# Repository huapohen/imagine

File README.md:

# 灵伴 LINGBAN / Imagine

透明晶鼠中的原创微型城堡，与电脑上的主动办公伙伴。当前交付是**可运行软件、固件与数字工程原型、商业与路演资料、AI概念影片**；实物样机、认证与量产尚待验证。

## 打开交付

- [本地资料中心](http://127.0.0.1:8766/)：产品图、全部文档、概念影片与评审资料。
- [16页商业计划PDF](pitch/business-plan/lingban-business-plan.pdf) · [商业计划源文](docs/business/business-plan.md)
- [18页可编辑PPTX](pitch/deliverables/final-20260906/lingban-vc-deck.pptx) · [PDF](pitch/deliverables/final-20260906/lingban-vc-deck.pdf) · [离线HTML](pitch/deliverables/final-20260906/lingban-vc-deck.html)
- [3分钟与8分钟逐字稿](docs/business/pitch-scripts.md) · [60个投资人问题](docs/business/investor-qa-60.md)
- [软件启动说明](software/README.md) · [模型接入与真实测试](docs/software/MODEL_INTEGRATION.md) · [固件](firmware/README.md)
- [CAD/PCB工程交接](hardware/COMPLETION.md) · [工厂RFQ](docs/manufacturing-commercial/rfq-template.md) · [独立硬件评审](docs/verification/HARDWARE_REVIEW.md)
- [八条影片与制作验证](media/FINAL_REPORT.md) · [私有GitHub仓库](https://github.com/huapohen/imagine)

## 本地运行

Python 3.9+，软件服务仅使用标准库：

```sh
./software/start.sh
```

按终端显示的员工/企业链接进入。角色令牌是访问凭据，只保存在页面内存；不要把带令牌的链接放进报告。所有默认演示数据均为合成数据，审批结果只进入本地outbox。

本次交付已在8765启动默认离线服务。当前角色链接记录在权限0600、Git忽略且资料服务不提供访问的`.local/demo-server.log`；可在本机终端查看。用户既有Chrome配置曾拦截该端口，未关闭浏览器保护；隔离浏览器验收已通过，录屏可直接查看。

另开终端运行资料中心：

```sh
python3 scripts/serve_workspace.py
```

临时模型测试使用根目录已被Git忽略的`.env`，须按[模型说明](docs/software/MODEL_INTEGRATION.md)显式开启。默认模型为`gpt-6-astra`、推理强度`medium`；模型负责合成场景草稿，本地权限、本人确认和调用预算保持有效。临时配置不进入镜像、交付压缩包或生产环境。

## 验证与交付边界

[最终验收矩阵](docs/verification/RELEASE_READINESS.md)记录自动化、浏览器、协议、固件编译、CAD、KiCad与视频的实际证据及未验证项。

299元是1000台情景下核心版的目标售价；108元制造成本和66.51元单位贡献是模型估算。五台EVT样机的开发板、透明件和装配成本单独计算。融资500万元是建议方案，60万元精简经营模型单独列示，没有收入或融资实绩假设。

企业只获得本人明确分享的业务结果与至少五人的聚合。人数阈值不代表匿名化；不做秘密采集、键盘记录、情绪/生理员工评分或自动雇佣决策。

EVT-A采用OEM USB HID鼠标总成与独立ESP32-S3交互模块、两路USB连接，电脑承担AI。设备唯一线协议是LB1 ASCII + CRC16；MCP 2025-06-18与A2A 0.3.0是本地实现子集。固件可编译、数字检查通过都不能替代实际通电、ESD/EMC、人体工学和工厂DFM签字；制造文件保持**NOT-FOR-FAB**。

大体积影片和制造ZIP通过私有GitHub Release附件分发，源码、财务、文档和精确哈希清单保留在Git。仅克隆仓库时，按[附件清单](docs/operations/RELEASE_ASSETS.md)恢复媒体。没有联系厂家/投资人、租GPU或额外购买工具。

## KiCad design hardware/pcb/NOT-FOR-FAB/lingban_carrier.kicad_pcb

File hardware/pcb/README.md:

# ESP32-S3 交互载板 EVT-A

`NOT-FOR-FAB/lingban_carrier.kicad_pro` 为可编辑工程；同目录包含原理图、实际双面走线PCB、自包含符号/封装库。36×76×1.6mm，2层1oz假设，0.25mm线宽，0.65/0.30mm过孔。所有输出仅工程评审用。

本载板只含插座、限流/上拉阻容、屏/LED/触摸/物理开关线束接口；ESP32-S3、RGB灯、屏幕与DPDT是外部器件。原理图所有引脚是无源载板触点，ERC只证明本载板连接规则；不证明ESP电气配置或外接器件正确。D1为DNI ESD占位，量产必须冻结真实TVS并更改封装/复验。

复现：仓库根运行 `python3 hardware/pcb/build_pcb.py --sync-existing`、`python3 hardware/pcb/finalize_project.py`、`python3 hardware/pcb/export_and_verify.py`。最后一条真实调用KiCad9.0.7，强制--schematic-parity及--exit-code-violations，同时记录独立几何DRC、ERC并导出制造文件。`gerber-review-only/`不是下单包；禁止仅因DRC/ERC通过即生产。

官方pinout/协议见`../specs/`；供电、线束、装配、成本与未验证项见`../../docs/hardware/engineering-and-manufacturing.md`。PCB顶面箭头方向尚需丝印完善，按J1/J3官方脚1及方形焊盘识别。PnP.csv为设计清单，PnP-kicad.csv为KiCad导出坐标；优先后者并由贴片厂核对底面旋转、原点和DNI。

`build_pcb.py --sync-existing`与`semantic_sync.py`只统一局部标签的完整网名、明确NC单脚网、符号path和机械孔board_only属性，不改铜线坐标。普通全量生成也会调用同一逻辑，未新增忽略规则。H1–H4的exclude_from_bom/pos是真实板上专用机械语义；采购BOM不列机械孔。49功能节点、33个无铜NC节点共82项与KiCad导出网表逐项匹配，检查不删除/前缀。

`sexpr.py`随本目录交付；工具环境不进入ZIP。设备接口只使用LB1；USB-UART115200、GPIO4–10及N8R8按已实装配置冻结，见specs/。

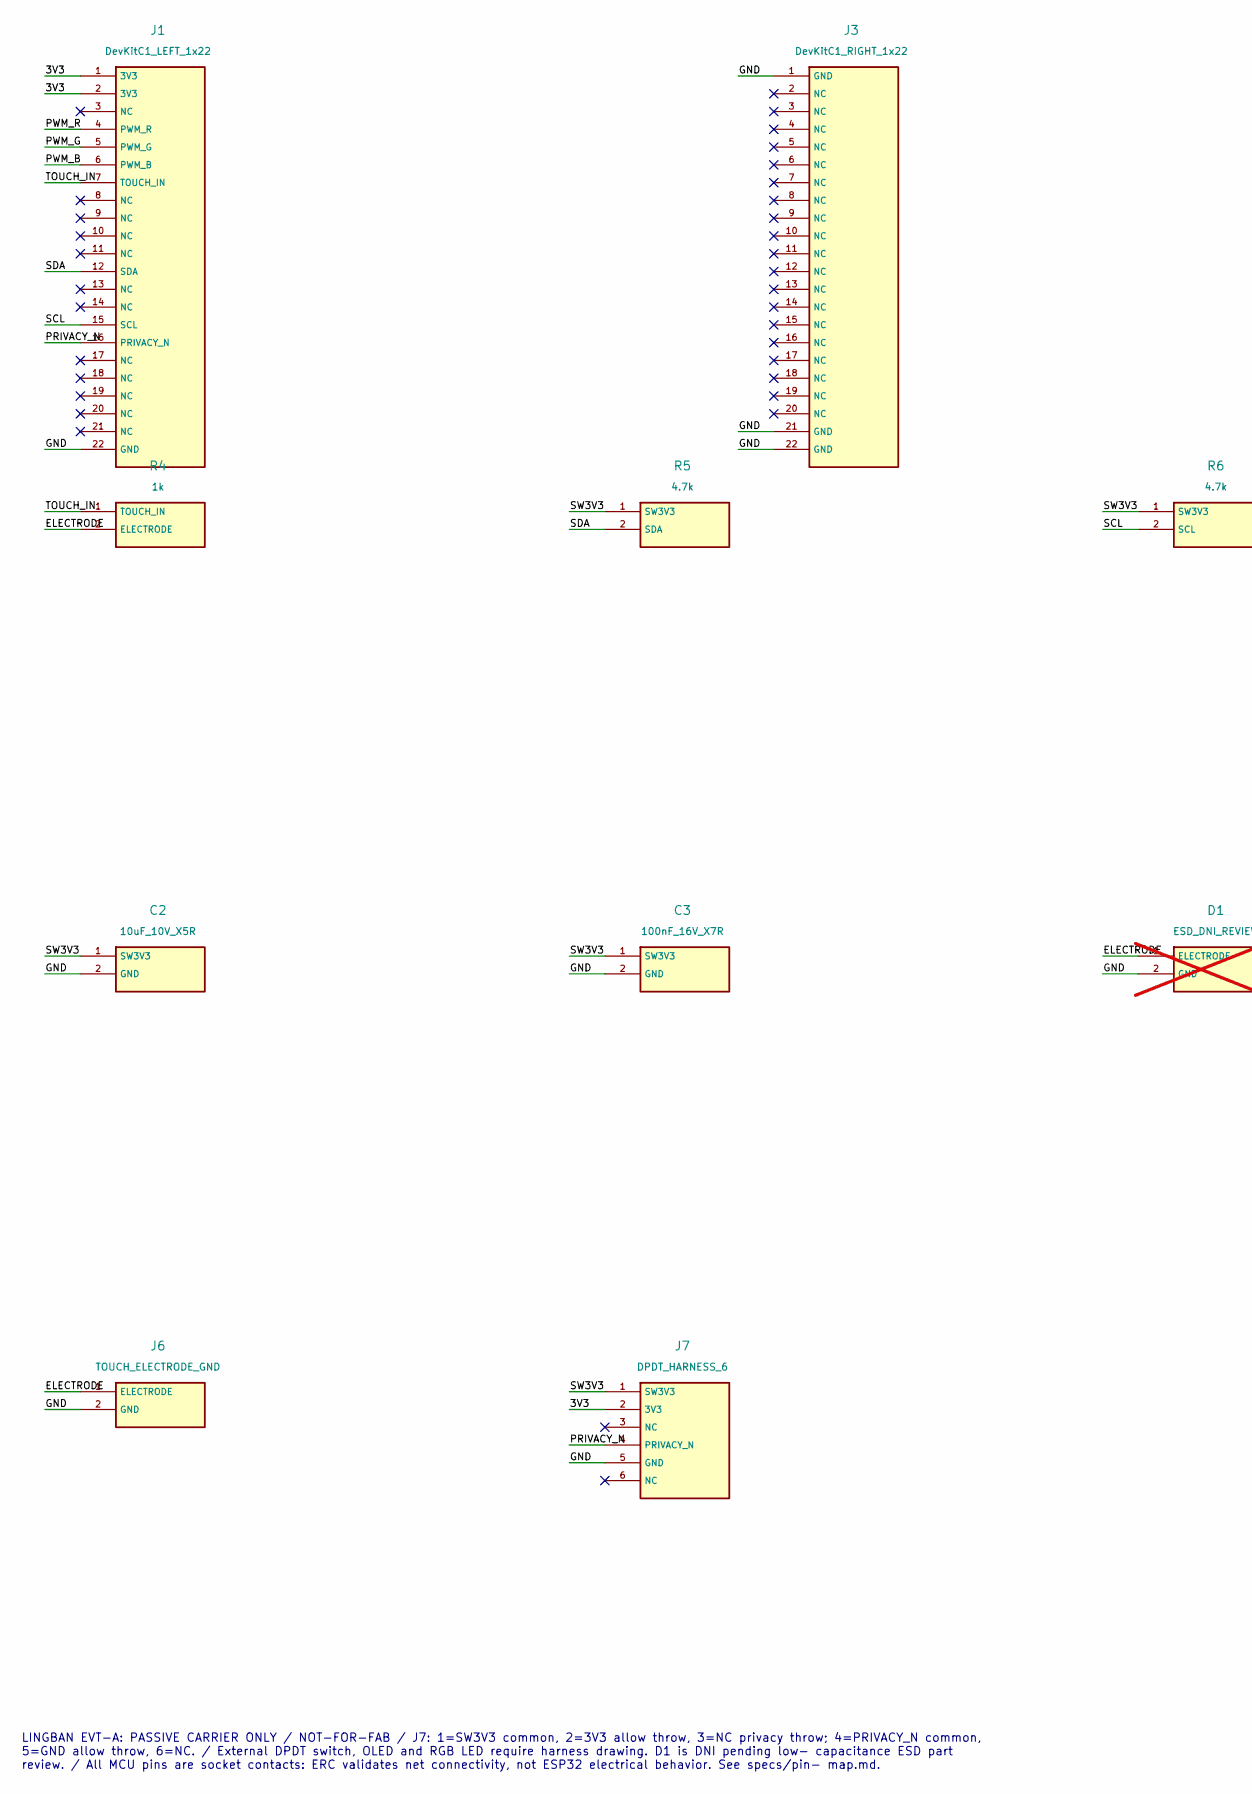
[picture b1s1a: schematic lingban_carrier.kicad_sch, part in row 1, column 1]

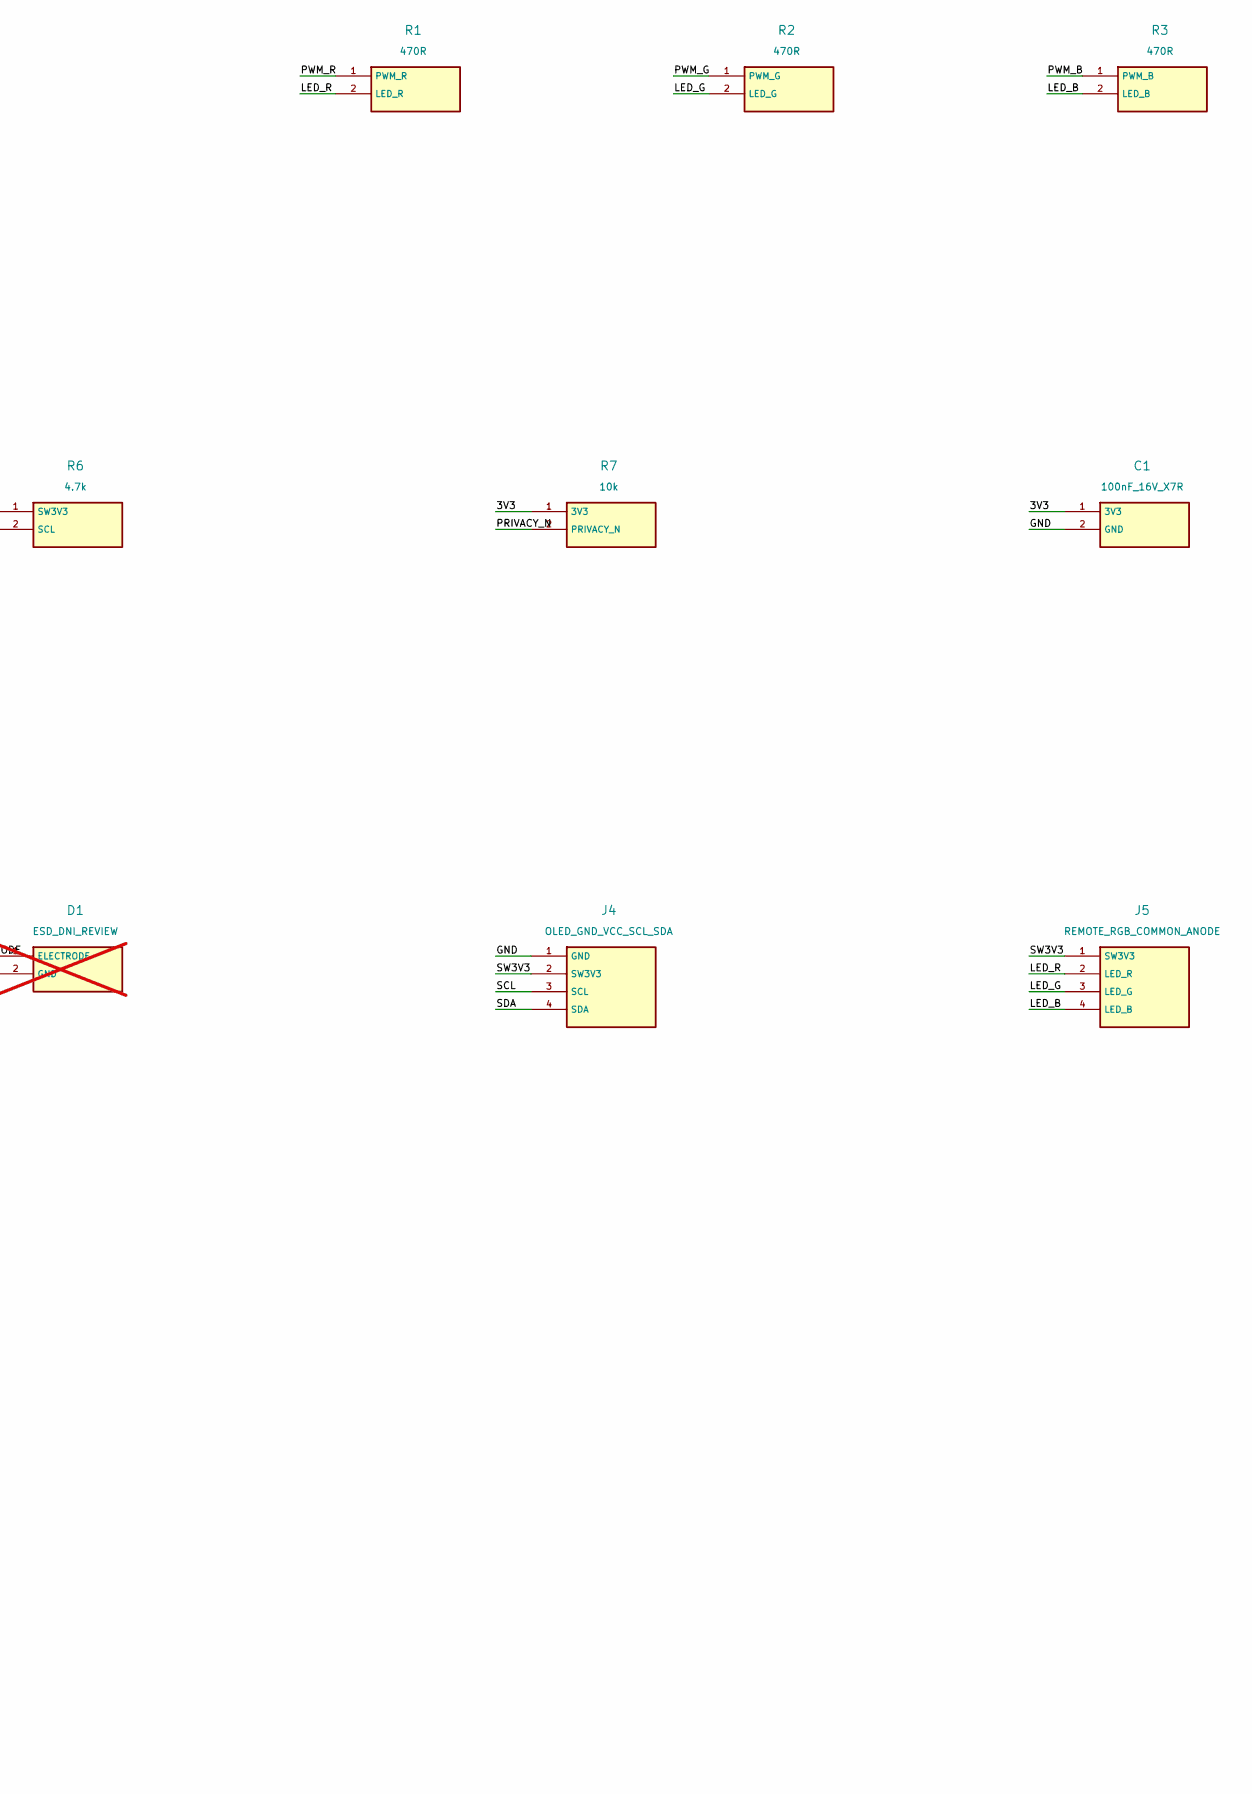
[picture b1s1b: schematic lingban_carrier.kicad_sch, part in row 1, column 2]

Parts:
C1: 100nF_16V_X7R; C1
C2: 10uF_10V_X5R; C2
C3: 100nF_16V_X7R; C3
D1: ESD_DNI_REVIEW; D1; not fitted
J1: DevKitC1_LEFT_1x22; J1
J3: DevKitC1_RIGHT_1x22; J3
J4: OLED_GND_VCC_SCL_SDA; J4
J5: REMOTE_RGB_COMMON_ANODE; J5
J6: TOUCH_ELECTRODE_GND; J6
J7: DPDT_HARNESS_6; J7
R1: 470R; R1
R2: 470R; R2
R3: 470R; R3
R4: 1k; R4
R5: 4.7k; R5
R6: 4.7k; R6
R7: 10k; R7

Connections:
/3V3: C1.1 (3V3), J1.1 (3V3), J1.2 (3V3), J7.2 (3V3), R7.1 (3V3)
/ELECTRODE: D1.1 (ELECTRODE), J6.1 (ELECTRODE), R4.2 (ELECTRODE)
/GND: C1.2 (GND), C2.2 (GND), C3.2 (GND), D1.2 (GND), J1.22 (GND), J3.1 (GND), J3.21 (GND), J3.22 (GND), J4.1 (GND), J6.2 (GND), J7.5 (GND)
/LED_B: J5.4 (LED_B), R3.2 (LED_B)
/LED_G: J5.3 (LED_G), R2.2 (LED_G)
/LED_R: J5.2 (LED_R), R1.2 (LED_R)
/PRIVACY_N: J1.16 (PRIVACY_N), J7.4 (PRIVACY_N), R7.2 (PRIVACY_N)
/PWM_B: J1.6 (PWM_B), R3.1 (PWM_B)
/PWM_G: J1.5 (PWM_G), R2.1 (PWM_G)
/PWM_R: J1.4 (PWM_R), R1.1 (PWM_R)
/SCL: J1.15 (SCL), J4.3 (SCL), R6.2 (SCL)
/SDA: J1.12 (SDA), J4.4 (SDA), R5.2 (SDA)
/SW3V3: C2.1 (SW3V3), C3.1 (SW3V3), J4.2 (SW3V3), J5.1 (SW3V3), J7.1 (SW3V3), R5.1 (SW3V3), R6.1 (SW3V3)
/TOUCH_IN: J1.7 (TOUCH_IN), R4.1 (TOUCH_IN)

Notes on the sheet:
LINGBAN EVT-A: PASSIVE CARRIER ONLY / NOT-FOR-FAB / J7: 1=SW3V3 common, 2=3V3 allow throw, 3=NC privacy throw; 4=PRIVACY_N common, 5=GND allow throw, 6=NC. / External DPDT switch, OLED and RGB LED require harness drawing. D1 is DNI pending low- capacitance ESD part review. / All MCU pins are socket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

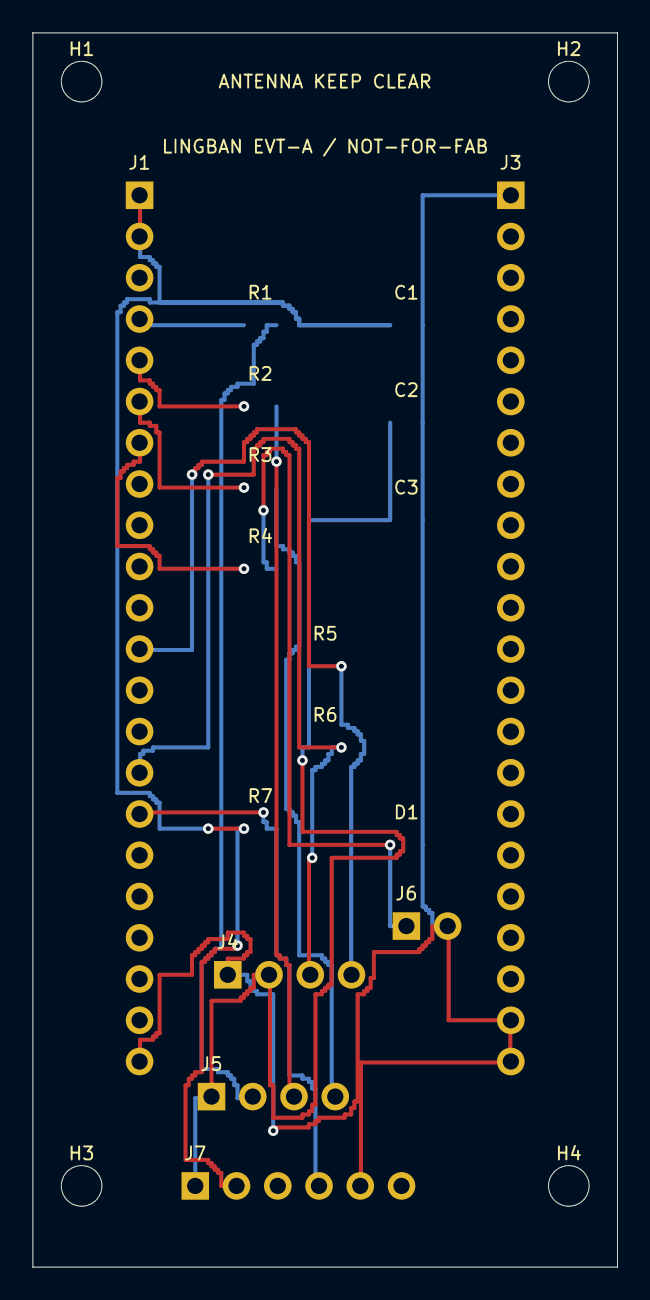
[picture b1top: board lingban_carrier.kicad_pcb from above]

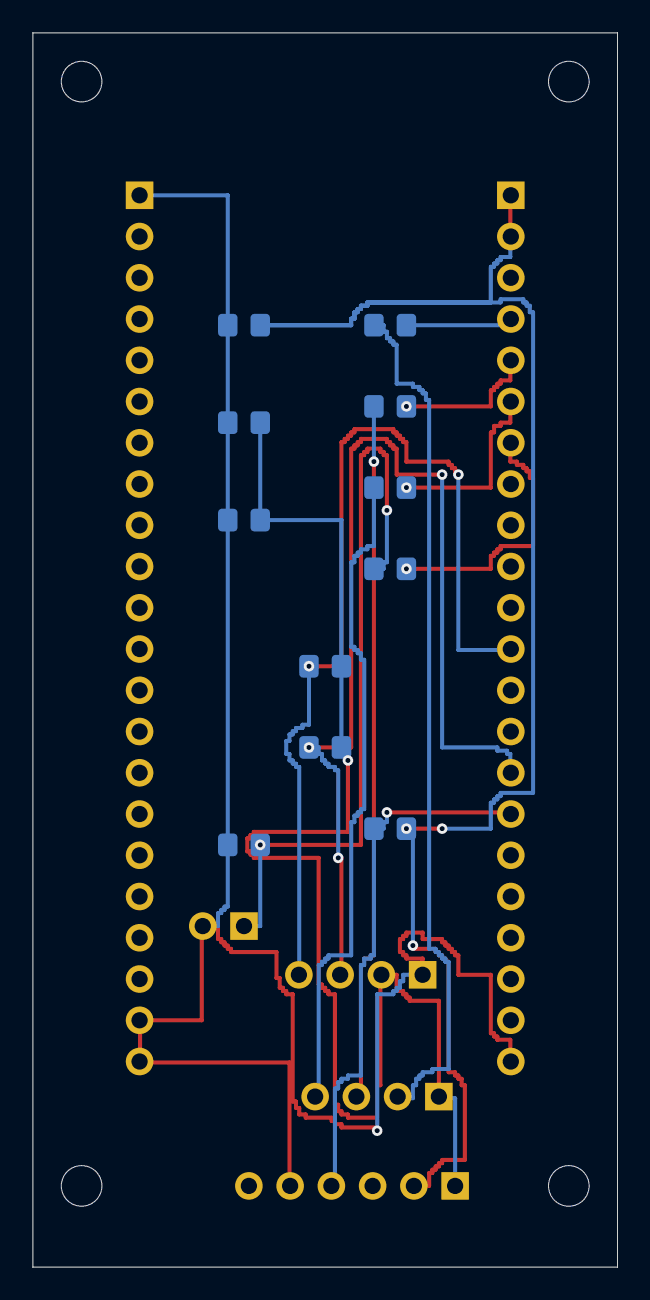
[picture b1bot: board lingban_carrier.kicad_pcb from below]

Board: 2 copper layers, 36.0 x 76.0 mm, 21 parts (11 on the bottom side), 14 nets.

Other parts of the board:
H1: M2_CLEARANCE; H1
H2: M2_CLEARANCE; H2
H3: M2_CLEARANCE; H3
H4: M2_CLEARANCE; H4

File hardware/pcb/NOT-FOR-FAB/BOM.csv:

Reference,Value,Footprint,Qty,Assembly,Qualification
J1,DevKitC1_LEFT_1x22,LINGBAN:J1,1,fit,unqualified engineering estimate; verify exact supplier drawing
J3,DevKitC1_RIGHT_1x22,LINGBAN:J3,1,fit,unqualified engineering estimate; verify exact supplier drawing
R1,470R,LINGBAN:R1,1,fit,unqualified engineering estimate; verify exact supplier drawing
R2,470R,LINGBAN:R2,1,fit,unqualified engineering estimate; verify exact supplier drawing
R3,470R,LINGBAN:R3,1,fit,unqualified engineering estimate; verify exact supplier drawing
R4,1k,LINGBAN:R4,1,fit,unqualified engineering estimate; verify exact supplier drawing
R5,4.7k,LINGBAN:R5,1,fit,unqualified engineering estimate; verify exact supplier drawing
R6,4.7k,LINGBAN:R6,1,fit,unqualified engineering estimate; verify exact supplier drawing
R7,10k,LINGBAN:R7,1,fit,unqualified engineering estimate; verify exact supplier drawing
C1,100nF_16V_X7R,LINGBAN:C1,1,fit,unqualified engineering estimate; verify exact supplier drawing
C2,10uF_10V_X5R,LINGBAN:C2,1,fit,unqualified engineering estimate; verify exact supplier drawing
C3,100nF_16V_X7R,LINGBAN:C3,1,fit,unqualified engineering estimate; verify exact supplier drawing
D1,ESD_DNI_REVIEW,LINGBAN:D1,1,DNI,unqualified engineering estimate; verify exact supplier drawing
J4,OLED_GND_VCC_SCL_SDA,LINGBAN:J4,1,fit,unqualified engineering estimate; verify exact supplier drawing
J5,REMOTE_RGB_COMMON_ANODE,LINGBAN:J5,1,fit,unqualified engineering estimate; verify exact supplier drawing
J6,TOUCH_ELECTRODE_GND,LINGBAN:J6,1,fit,unqualified engineering estimate; verify exact supplier drawing
J7,DPDT_HARNESS_6,LINGBAN:J7,1,fit,unqualified engineering estimate; verify exact supplier drawing
